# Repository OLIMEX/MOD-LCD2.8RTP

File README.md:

# MOD-LCD2.8RTP
TFT COLOR LCD module with [UEXT connector](https://www.olimex.com/Products/Modules/) for
[ESP32-EVB](https://www.olimex.com/Products/IoT/ESP32/ESP32-EVB/open-source-hardware) and
[ESP32-POE](https://www.olimex.com/Products/IoT/ESP32/ESP32-POE/open-source-hardware)

**Using MOD-LCD2.8RTP requires non-standard SPI for the display and I2C for the touch screen** 

The non-standard part of the SPI is the lack of MISO which is Data/Command selection pin (refer to controller's datasheet) which has to be set as output.

UEXT pinout:

|UEXT column 1|UEXT column 2|Function|
|---|---|---|
|1 - 3.3V |2 - GND|Power pins|
|3 - NOT USED|4 - NOT USED|UART pins not used|
|5 - SCL|6 - SDA|I2C pins used for touch component|
|7 - D/C|8 - MOSI|SPI pins sans MISO used for display|
|9 - CLK|10 - CS|SPI CLK/CS for display|

If you are using I2C, then the RX wire can also be used to control the brightness. This requires midfying the SJ2 jumper. Refer to the schematic around FET1.

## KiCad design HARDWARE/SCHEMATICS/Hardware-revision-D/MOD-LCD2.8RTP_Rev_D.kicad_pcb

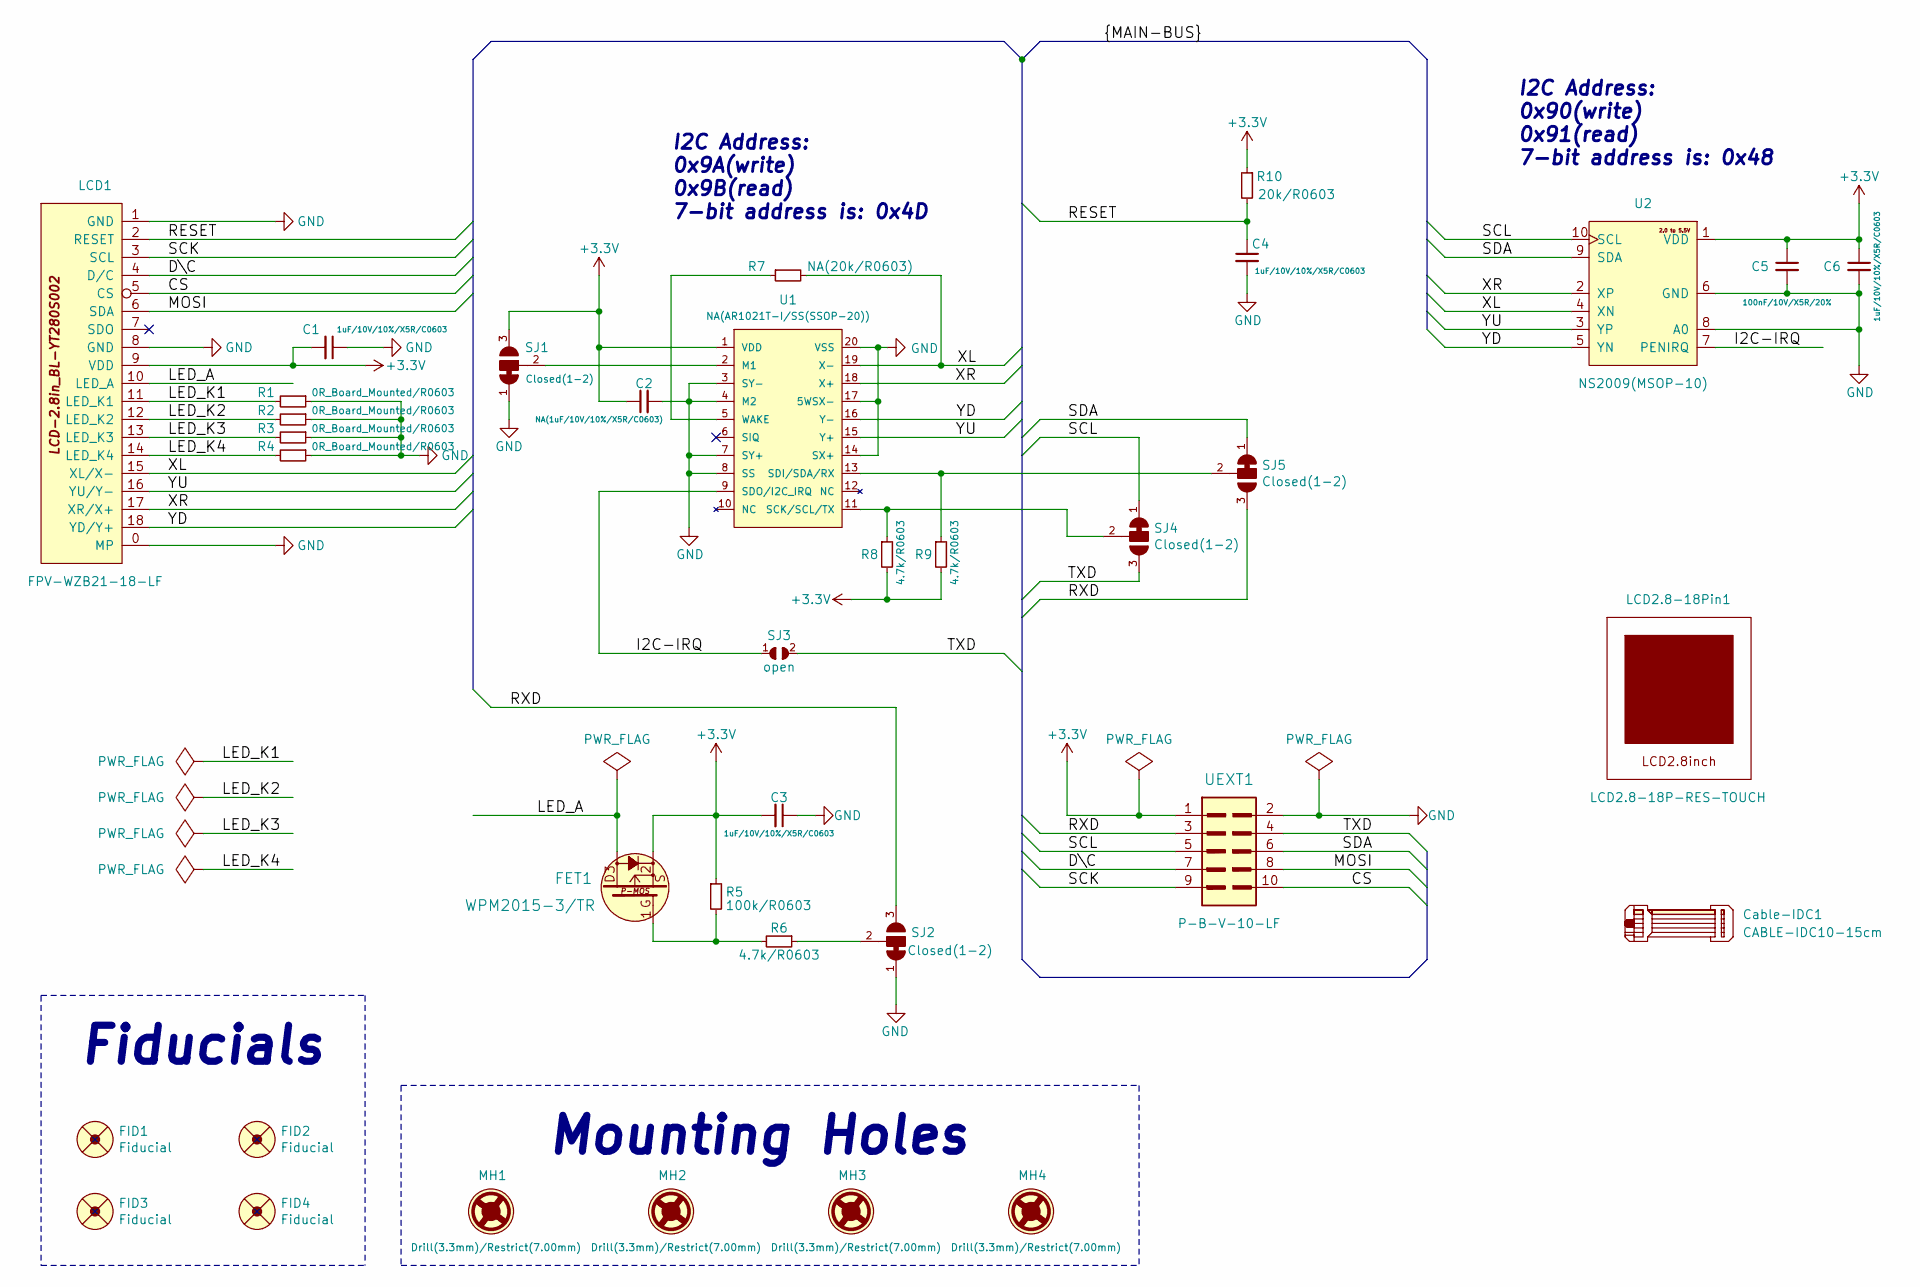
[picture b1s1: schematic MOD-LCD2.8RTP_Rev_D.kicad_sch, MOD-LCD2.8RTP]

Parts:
C1, C3, C4, C6: 1uF/10V/10%/X5R/C0603; C_0603_5MIL_DWS
C2: NA(1uF/10V/10%/X5R/C0603); C_0603_5MIL_DWS
C5: 100nF/10V/X5R/20%; C_0402_5MIL_DWS
Cable-IDC1: CABLE-IDC10-15cm; Cable-IDC
FET1: WPM2015-3/TR; SOT23
FID1, FID3: Fiducial; Fiducial1x3
FID2, FID4: Fiducial; Fiducial1x3_Paste
LCD1: FPV-WZB21-18-LF; LCD-2.8in_BL-YT280S002(FPV-WZB21-18-LF)
LCD2.8-18Pin1: LCD2.8-18P-RES-TOUCH; LCD2.8-18Pin
MH1, MH2, MH3, MH4: Drill(3.3mm)/Restrict(7.00mm); Mounting_Hole_Drill-3.3mm_Clerance-7mm
R1, R2, R3, R4: 0R_Board_Mounted/R0603; R_0603_5MIL_0R(Board_Mounted)
R5: 100k/R0603; R_0603_5MIL_DWS
R6, R8, R9: 4.7k/R0603; R_0603_5MIL_DWS
R7: NA(20k/R0603); R_0603_5MIL_DWS
R10: 20k/R0603; R_0603_5MIL_DWS
SJ1, SJ2, SJ4, SJ5: Closed(1-2); SJ_2_SMALL_12_TIED
SJ3: open; SJ
U1: NA(AR1021T-I/SS(SSOP-20)); SSOP-20W
U2: NS2009(MSOP-10); MSOP-10_Pitch-0.5mm_3.00x3.00x1.00mm
UEXT1: P-B-V-10-LF; GBH-254-SMT-10

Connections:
+3.3V: C1.2, C2.1, C3.2, C5.1, C6.1, FET1.2, LCD1.9 (VDD), R5.1, R8.2, R9.2, R10.1, SJ1.3, U1.1 (VDD), U2.1 (VDD), UEXT1.1
/CS: LCD1.5 (CS), UEXT1.10
/D\C: LCD1.4 (D/C), UEXT1.7
/I2C-IRQ: SJ3.1, U1.9 (SDO/I2C_IRQ), U2.7 (PENIRQ)
/LED_A: FET1.3, LCD1.10 (LED_A)
/LED_K1: LCD1.11 (LED_K1), R1.2
/LED_K2: LCD1.12 (LED_K2), R2.2
/LED_K3: LCD1.13 (LED_K3), R3.2
/LED_K4: LCD1.14 (LED_K4), R4.2
/MOSI: LCD1.6 (SDA), UEXT1.8
/RESET: C4.1, LCD1.2 (RESET), R10.2
/RXD: SJ2.3, SJ5.3, UEXT1.3
/SCK: LCD1.3 (SCL), UEXT1.9
/SCL: SJ4.1, U2.10 (SCL), UEXT1.5
/SDA: SJ5.1, U2.9 (SDA), UEXT1.6
/TXD: SJ3.2, SJ4.3, UEXT1.4
/XL: LCD1.15 (XL/X-), R7.2, U1.19 (X-), U2.4 (XN)
/XR: LCD1.17 (XR/X+), U1.18 (X+), U2.2 (XP)
/YD: LCD1.18 (YD/Y+), U1.16 (Y-), U2.5 (YN)
/YU: LCD1.16 (YU/Y-), U1.15 (Y+), U2.3 (YP)
GND: C1.1, C2.2, C3.1, C4.2, C5.2, C6.2, LCD1.0 (MP), LCD1.1 (GND), LCD1.8 (GND), R1.1, R2.1, R3.1, R4.1, SJ1.1, SJ2.1, U1.3 (SY-), U1.4 (M2), U1.7 (SY+), U1.8 (SS), U1.14 (SX+), U1.17 (5WSX-), U1.20 (VSS), U2.6 (GND), U2.8 (A0), UEXT1.2
unnamed: FET1.1, R5.2, R6.2
unnamed: R6.1, SJ2.2
unnamed: SJ1.2, U1.2 (M1)
unnamed: R8.1, SJ4.2, U1.11 (SCK/SCL/TX)
unnamed: R9.1, SJ5.2, U1.13 (SDI/SDA/RX)
unnamed: R7.1, U1.5 (WAKE)

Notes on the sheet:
Fiducials
I2C Address: 0x90(write) 0x91(read) 7-bit address is: 0x48
Mounting Holes
I2C Address: 0x9A(write) 0x9B(read) 7-bit address is: 0x4D

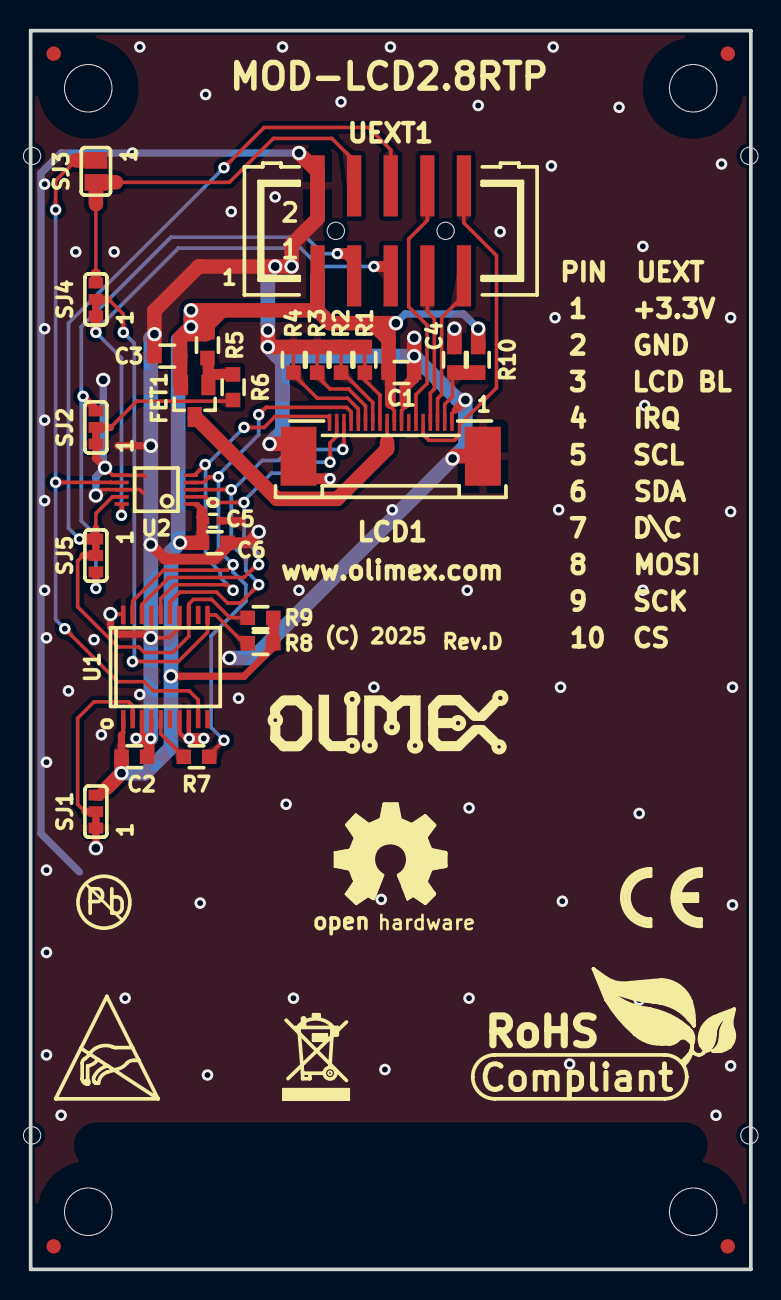
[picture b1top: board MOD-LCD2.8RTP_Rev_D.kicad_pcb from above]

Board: 2 copper layers, 50.0 x 86.0 mm, 44 parts (1 on the bottom side), 27 nets.

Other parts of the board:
Logo_Olimex_1, Logo_Olimex_2: OLIMEX_LOGO_TB
Sign_Antistatic: Sign_Antistatic
Sign_CE: CE_Sign
Sign_OSHW: LOGO_OPENHARDWARE_8x8
Sign_PB-Free: LOGO_PBFREE
Sign_Recyclebin: LOGO_RECYCLEBIN_1
Sign_RoHS_1: Sign_RoHS_1

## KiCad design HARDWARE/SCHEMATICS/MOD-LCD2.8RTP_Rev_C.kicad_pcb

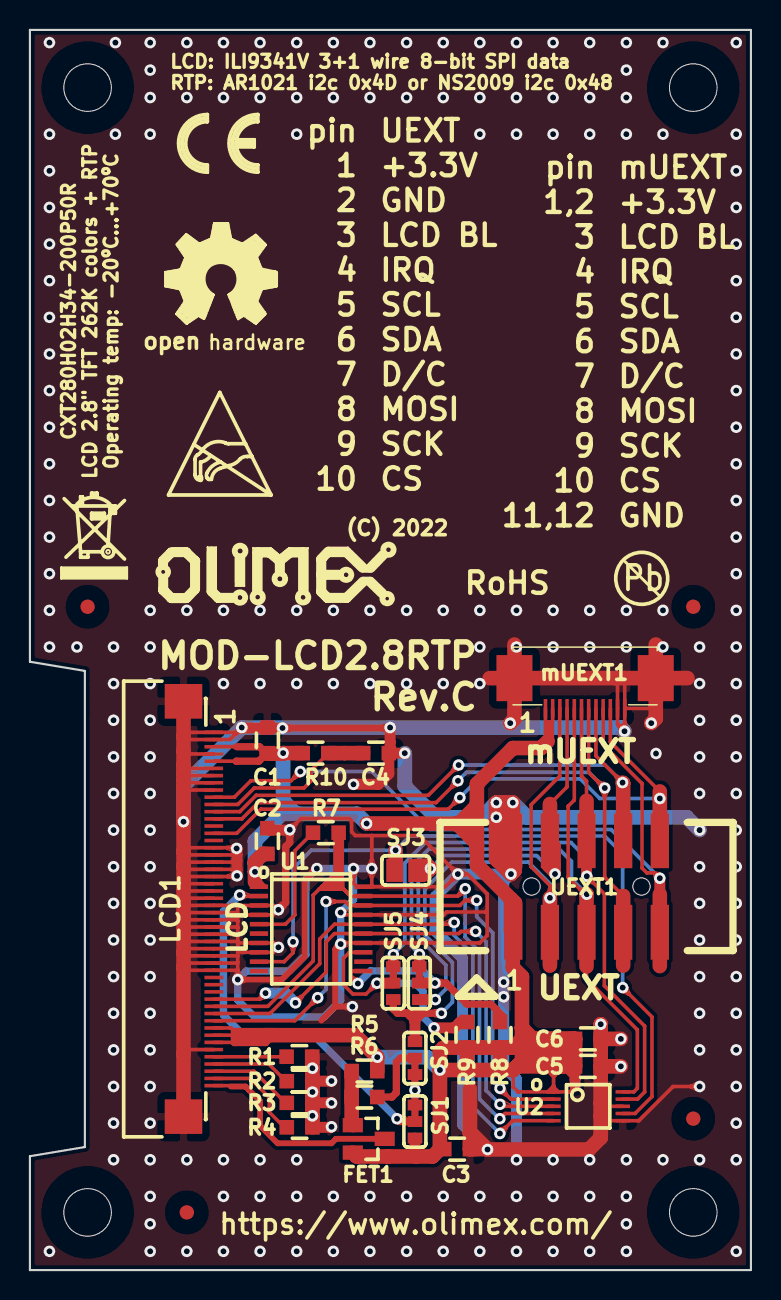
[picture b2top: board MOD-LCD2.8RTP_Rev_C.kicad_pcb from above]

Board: 2 copper layers, 50.0 x 86.0 mm, 42 parts (1 on the bottom side), 27 nets.

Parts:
C1, C3, C4, C6: 1uF/10V/10%/X5R/C0603; C_0603_5MIL_DWS
C2: NA(1uF/10V/10%/X5R/C0603); C_0603_5MIL_DWS
C5: 100nF/Y5V/50VDC/20%/C0603; C_0603_5MIL_DWS
FET1: WPM2015-3/TR; SOT23
FID1, FID2, FID3, FID4: Val**; Fiducial1x3_transp
LCD1: (CXT280H02H34-200P50R)+(FPV-WZB21-50-LF); FPV-WZB21-50-LF
Logo_Olimex_1, Logo_Olimex_2: OLIMEX_LOGO_TB
MH1, MH2, MH3, MH4: Mounting_hole_3.3mm
R1, R2, R3, R4: 22R/R0603; R_0603_5MIL_DWS
R5: 100k/R0603; R_0603_5MIL_DWS
R6, R8, R9: 4.7k/R0603; R_0603_5MIL_DWS
R7: NA(20k/R0603); R_0603_5MIL_DWS
R10: 20k/R0603; R_0603_5MIL_DWS
SJ1, SJ2, SJ4, SJ5: Closed(1-2); SJ_2_SMALL_12_TIED
SJ3: open; SJ
Sign_Antistatic: Sign_Antistatic
Sign_CE: CE_Sign
Sign_OSHW: LOGO_OPENHARDWARE_8x8
Sign_PB-Free: LOGO_PBFREE
Sign_Recyclebin: LOGO_RECYCLEBIN_1
U1: NA(AR1021T-I/SS(SSOP-20)); SSOP-20W
U2: NS2009(MSOP-10); MSOP-10_Pitch-0.5mm_3.00x3.00x1.00mm
UEXT1: (P-B-V-10-LF)+(CABLE-IDC10-15CM); UEXTM-SMD
mUEXT1: FPV-WZA21-12-LF; FPV-WZB21-12-LF

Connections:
+3V3: C1.2, C2.1, C3.2, C5.1, C6.1, FET1.2, LCD1.3, LCD1.5, LCD1.42, LCD1.43, LCD1.44, R5.1, R8.2, R9.2, R10.1, SJ1.3, U1.1, U2.1, UEXT1.1, mUEXT1.1, mUEXT1.2
/CS: LCD1.15, UEXT1.10, mUEXT1.10
/D\C: LCD1.13, UEXT1.7, mUEXT1.7
/I2C-IRQ: SJ3.1, U1.9, U2.7
/LEDA: FET1.3, LCD1.50
/LEDK0: LCD1.49, R4.2
/LEDK1: LCD1.48, R3.2
/LEDK2: LCD1.47, R2.2
/LEDK3: LCD1.46, R1.2
/MOSI: LCD1.12, UEXT1.8, mUEXT1.8
/RESET: C4.1, LCD1.11, R10.2
/RXD: SJ2.3, SJ5.3, UEXT1.3, mUEXT1.3
/SCK: LCD1.10, UEXT1.9, mUEXT1.9
/SCL: SJ4.1, U2.10, UEXT1.5, mUEXT1.5
/SDA: SJ5.1, U2.9, UEXT1.6, mUEXT1.6
/TXD: SJ3.2, SJ4.3, UEXT1.4, mUEXT1.4
/XL: LCD1.39, R7.2, U1.19, U2.4
/XR: LCD1.41, U1.18, U2.2
/YD: LCD1.40, U1.16, U2.5
/YU: LCD1.38, U1.15, U2.3
GND: C1.1, C2.2, C3.1, C4.2, C5.2, C6.2, LCD1.0, LCD1.1, LCD1.2, LCD1.4, LCD1.6, LCD1.7, LCD1.8, LCD1.9, LCD1.17, LCD1.18, LCD1.19, LCD1.20, LCD1.21, LCD1.22, LCD1.23, LCD1.24, LCD1.25, LCD1.26, LCD1.27, LCD1.28, LCD1.29, LCD1.30, LCD1.31, LCD1.32, LCD1.33, LCD1.34, LCD1.45, R1.1, R2.1, R3.1, R4.1, SJ1.1, SJ2.1, U1.3, U1.4, U1.7, U1.8, U1.14, U1.17, U1.20, U2.6, U2.8, UEXT1.2, mUEXT1.0, mUEXT1.11, mUEXT1.12
unnamed: FET1.1, R5.2, R6.2
unnamed: R6.1, SJ2.2
unnamed: R7.1, U1.5
unnamed: R8.1, SJ4.2, U1.11
unnamed: R9.1, SJ5.2, U1.13
unnamed: SJ1.2, U1.2

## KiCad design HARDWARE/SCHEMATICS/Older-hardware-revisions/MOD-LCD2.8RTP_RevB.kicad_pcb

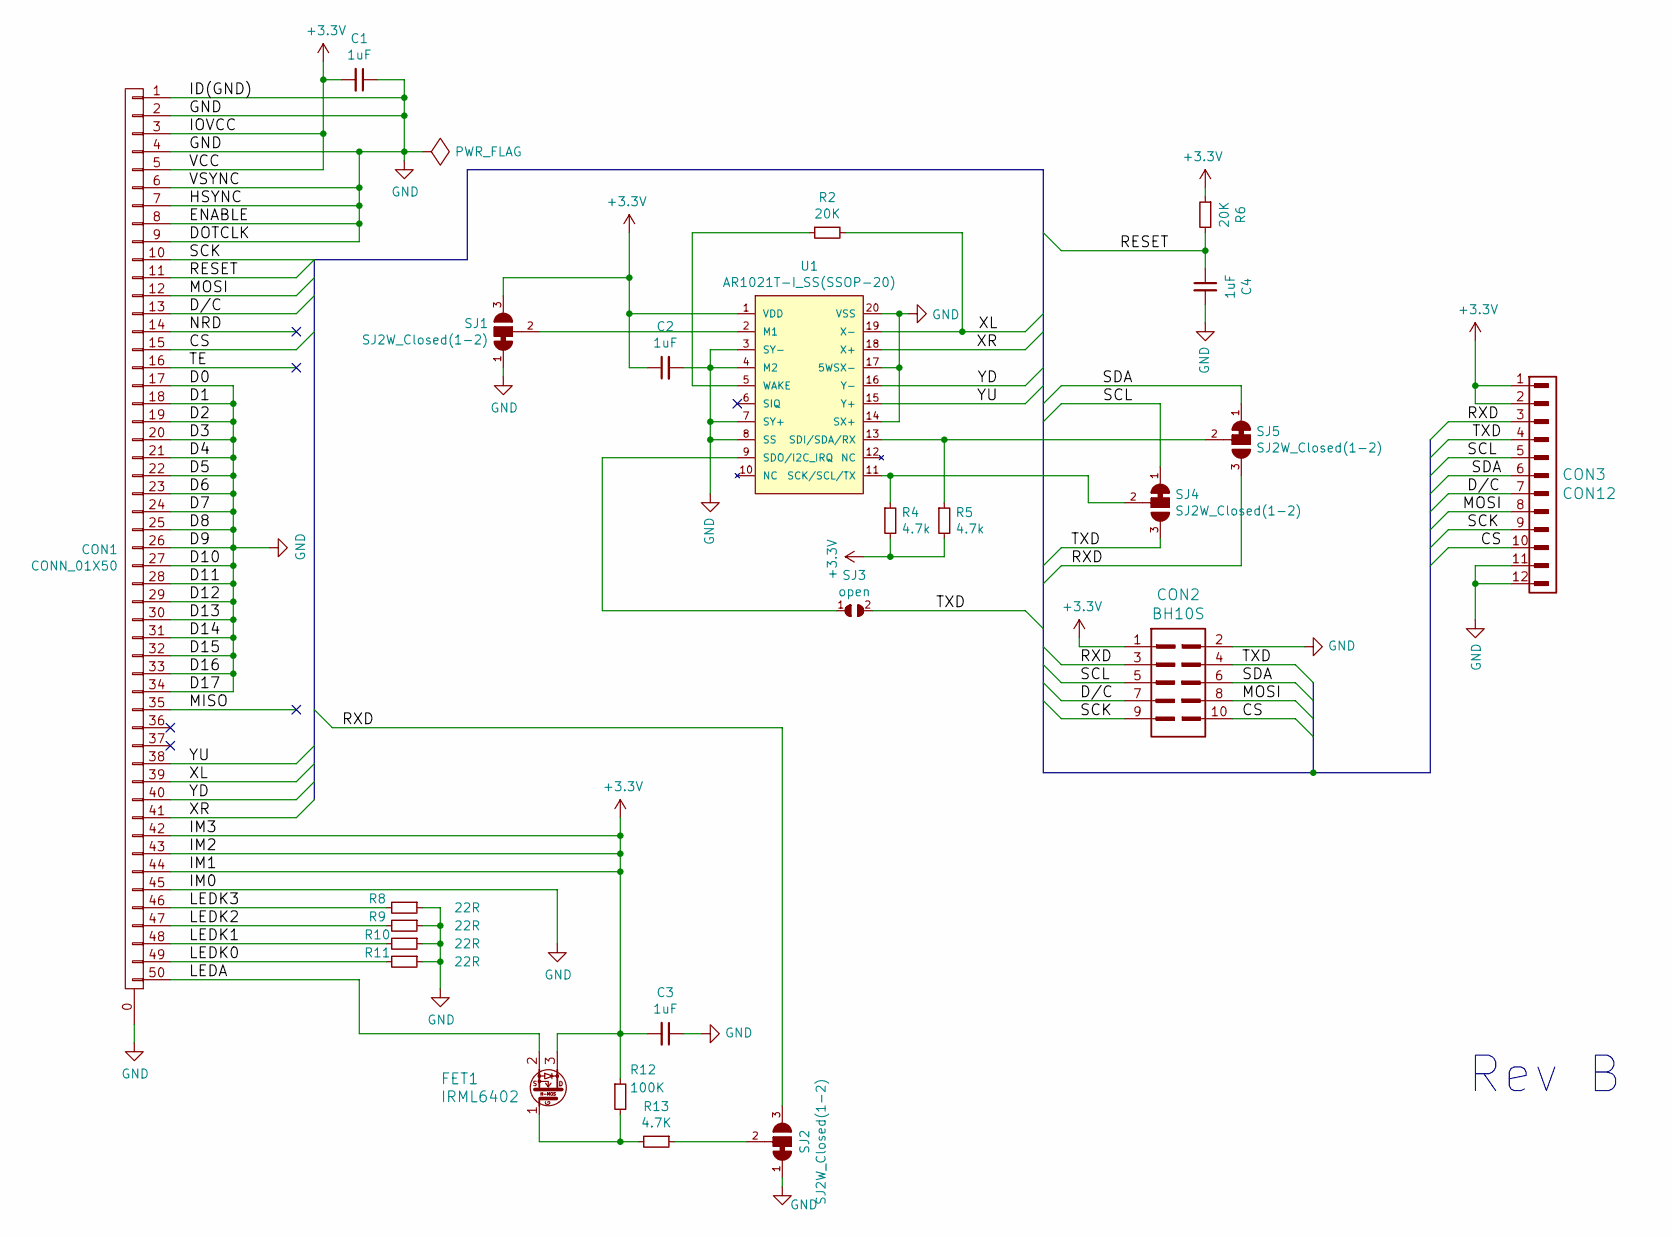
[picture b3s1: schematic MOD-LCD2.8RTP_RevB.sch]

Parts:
C1, C2, C3, C4: 1uF; C_0603_5MIL_DWS
CON1: CONN_01X50; FPV-WZA21-50-LF
CON2: BH10S; UEXTM-SMD
CON3: CON12; FPV-WZB21-12-LF
FET1: IRML6402; SOT23
R2, R6: 20K; R_0603_5MIL_DWS
R4, R5: 4.7k; R_0603_5MIL_DWS
R8, R9, R10, R11: 22R; R_0603_5MIL_DWS
R12: 100K; R_0603_5MIL_DWS
R13: 4.7K; R_0603_5MIL_DWS
SJ1, SJ2, SJ4, SJ5: SJ2W_Closed(1-2); SJ_2_SMALL_12_TIED
SJ3: open; SJ_2_SMALL
U1: AR1021T-I_SS(SSOP-20); SSOP-20

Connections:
+3V3: C1.2, C2.1, C3.2, CON1.3, CON1.5, CON1.42, CON1.43, CON1.44, CON2.1, CON3.1, CON3.2, FET1.3 (D), R4.2, R5.2, R6.1, R12.1, SJ1.3, U1.1 (VDD)
/CS: CON1.15, CON2.10, CON3.10
/D/C: CON1.13, CON2.7, CON3.7
/LEDA: CON1.50, FET1.2 (S)
/LEDK0: CON1.49, R11.2
/LEDK1: CON1.48, R10.2
/LEDK2: CON1.47, R9.2
/LEDK3: CON1.46, R8.2
/MISO: CON1.35
/MOSI: CON1.12, CON2.8, CON3.8
/NRD: CON1.14
/RESET: C4.1, CON1.11, R6.2
/RXD: CON2.3, CON3.3, SJ2.3, SJ5.3
/SCK: CON1.10, CON2.9, CON3.9
/SCL: CON2.5, CON3.5, SJ4.1
/SDA: CON2.6, CON3.6, SJ5.1
/TE: CON1.16
/TXD: CON2.4, CON3.4, SJ3.2, SJ4.3
/XL: CON1.39, R2.2, U1.19 (X-)
/XR: CON1.41 (P4), U1.18 (X+)
/YD: CON1.40, U1.16 (Y-)
/YU: CON1.38, U1.15 (Y+)
GND: C1.1, C2.2, C3.1, C4.2, CON1.0, CON1.1, CON1.2, CON1.4, CON1.6, CON1.7, CON1.8, CON1.9, CON1.17, CON1.18, CON1.19, CON1.20, CON1.21, CON1.22, CON1.23, CON1.24, CON1.25, CON1.26, CON1.27, CON1.28, CON1.29, CON1.30, CON1.31, CON1.32, CON1.33, CON1.34, CON1.45, CON2.2, CON3.0, CON3.11, CON3.12, R8.1, R9.1, R10.1, R11.1, SJ1.1, SJ2.1, U1.3 (SY-), U1.4 (M2), U1.7 (SY+), U1.8 (SS), U1.14 (SX+), U1.17 (5WSX-), U1.20 (VSS)
unnamed: FET1.1 (G), R12.2, R13.2
unnamed: R2.1, U1.5 (WAKE)
unnamed: R4.1, SJ4.2, U1.11 (SCK/SCL/TX)
unnamed: R5.1, SJ5.2, U1.13 (SDI/SDA/RX)
unnamed: R13.1, SJ2.2
unnamed: SJ1.2, U1.2 (M1)
unnamed: SJ3.1, U1.9 (SDO/I2C_IRQ)

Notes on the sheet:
Rev B

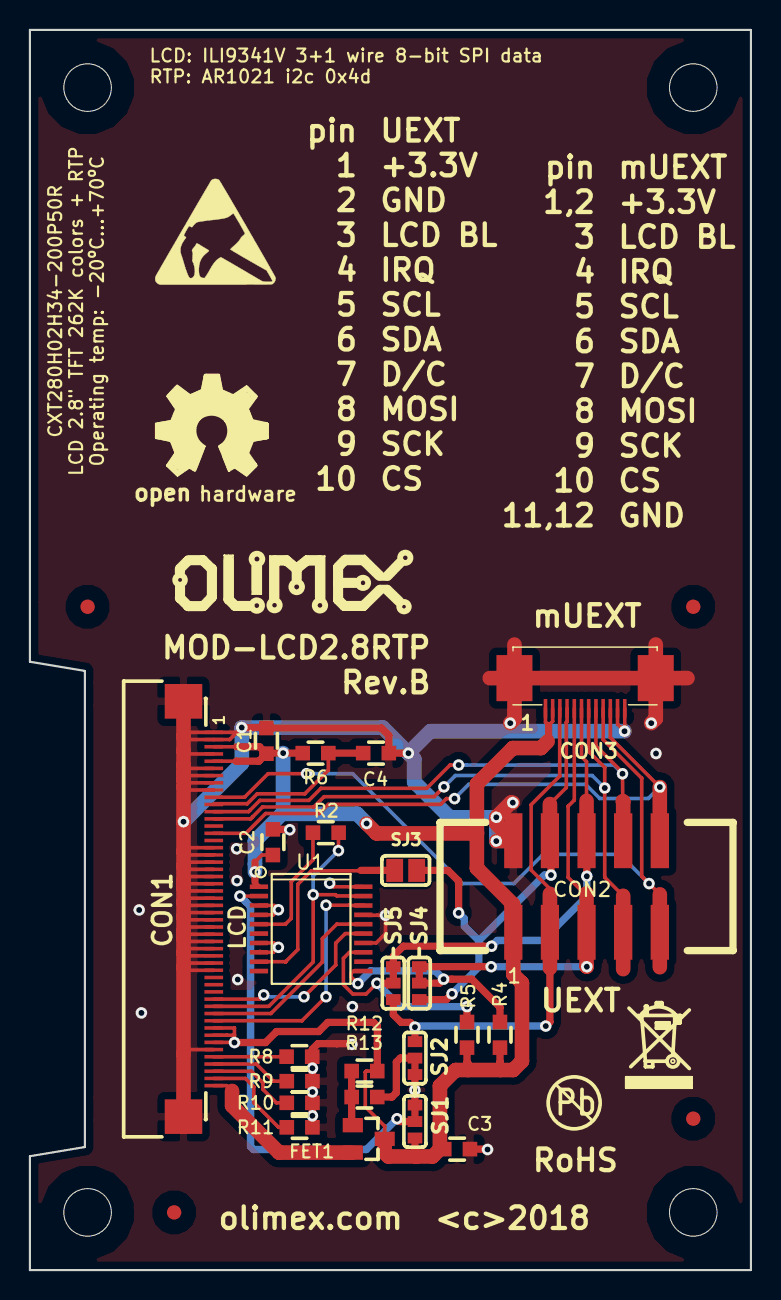
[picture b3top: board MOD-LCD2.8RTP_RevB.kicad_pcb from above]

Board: 2 copper layers, 50.0 x 86.0 mm, 32 parts (0 on the bottom side), 27 nets.

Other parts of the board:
MountingHole*: Mounting_hole_3.3mm
MountingHole*#2, MountingHole*#3, MountingHole*#4: Mounting_hole_3.3mm
Ref*: Val**; Fiducial1x3_transp
Ref*#2, Ref*#3, Ref*#4: Val**; Fiducial1x3_transp

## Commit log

2018-06-24 Add documentation from Olimex website
2018-06-25 update
    smal adjustments after testing
2018-10-23 Update
    Some info
2020-11-04 Add UEXT pinout defines for ESP32-PoE
2021-02-01 Update
    Corrected #if to match the correct preprocessor define macros of the respetive board.
2021-02-25 Update
    Arduino example patched to work with Olimexino-STM32F
2022-10-21 Update
    Added support for WROOM
2023-04-11 Update
    Update for NS2009 touch
2023-04-11 Update
    new ts datasheet
2023-10-09 Update graphicstest_olimex_NS2009.ino
    Added commented line with SPI initialization with lower frequency (30MHz) in case of usage of longer cable or UEXTx5
2023-10-11 Update
    Uploaded hardware revision C files
2024-05-10 Update
    Added hardware changes file.
2025-05-09 Update
    New hardware revision D
2025-05-09 Update
    Added more info about PCB changes.
2025-05-09 Update
    Extra documents for latest revisions.
2025-05-09 Update
    Dimensions for latest hardware revision

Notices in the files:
HARDWARE/SCHEMATICS/Hardware-revision-D/MOD-LCD2.8RTP_Rev_D.kicad_pcb:
(C) 2025
HARDWARE/SCHEMATICS/MOD-LCD2.8RTP_Rev_C.kicad_pcb:
(C) 2022
